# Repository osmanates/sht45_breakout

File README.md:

# SHT45 Breakout Kartı

Sensirion **SHT45** (±1.0 %RH, ±0.1 °C, I²C) nem ve sıcaklık sensörü için küçük bir breakout (modül) kartı.
Şema, PCB, Gerber, delik dosyası ve JLCPCB montaj (BOM/CPL) dosyaları bu depoda.

| Özellik | Değer |
|---|---|
| Kart boyutu | **16.0 × 19.8 mm**, 2 katman, 1.6 mm FR4, 2 adet M2 montaj deliği |
| Besleme | **1.08 … 3.6 V** (5 V ile çalışmaz, aşağıya bakın) |
| Arayüz | I²C, adres **0x44** (SHT45-AD1B), en fazla 1 MHz (Fm+) |
| Konnektör | J1: 1×4, 2.54 mm pin header, J2: 4 pinli JST XH (2.50 mm). İkisinde de sıra `VCC GND SCL SDA` |
| Parçalar | U1 SHT45 (DFN-4 1.5×1.5), C1 100 nF 0603, R1/R2 10 kΩ 0603, JP1 lehim köprüsü |

(Görseller KiCad'in değil, doğrudan üretilen Gerber dosyalarının `gerbv` ile çizilmiş halidir.
Alt yüz, kartın üstünden bakılıyormuş gibi gösterildiği için yazılar ters görünüyor. Düz okunan
hali `docs/pcb_bottom.png` dosyasında.)

## Tasarım kararları (Sensirion dokümanlarından)

Tasarımda şu belgeler kullanıldı: *Datasheet SHT4x v7.3*, *Design Guide for Humidity and
Temperature Sensors*, *Handling Instructions SHTxx*, *Contamination Guide*, *Creep Mitigation
SHT4x* ve *Heater Decontamination SHT4x* ([ürün sayfası](https://sensirion.com/products/catalog/SHT45)).

1. **Devre, datasheet Fig. 1'deki tipik uygulama devresiyle aynı:** SDA/SCL için 10 kΩ pull-up,
   VDD–VSS arasında 100 nF. Pull-up değeri, datasheet'teki minimum değerin (VDD ≥ 1.62 V için
   390 Ω) çok üzerinde.
2. **Land pattern datasheet Fig. 17'ye göre çizildi:** 0.5 × 0.3 mm pad'ler, 0.8 mm dikey ve 1.4 mm
   yatay aralık (KiCad'deki `Sensirion_DFN-4_…_SHT4x_NoCentralPad` footprint'i).
   **Orta pad (die pad) lehimlenmiyor** ve sensörün altında pad'ler dışında **bakır yok**
   (datasheet 5.3). Lehimlenmiş bir die pad, sensörün içindeki ısıtıcıyı soğutur (heat sink etkisi).
3. **Termal izolasyon:** Sensör, kartın geri kalanından iki adet 1.2 mm'lik freze yarığıyla ayrılmış
   4.4 mm genişliğinde bir "dil" üzerinde duruyor (Design Guide bölüm 3 / Fig. 8b, 11). Dile sadece 4 adet **0.15 mm**
   iz geçiyor. Dilde bakır dolgu (pour) yok. Böylece header'dan ve bağlı karttan gelen ısı sensöre
   daha az ulaşıyor.
4. **C1, sensörün VDD/VSS pinlerine doğrudan bağlı** (≈0.6 mm uzaklıkta). Isıtıcı çalışırken
   çekilen 100 mA'e varan akım darbeleri için bu yakınlık önemli.
5. **Pull-up'lar ve lehim köprüsü ana gövdede**, sensörden uzakta. **JP1** (alt yüzde, "PU")
   fabrikadan kapalı (köprülü) gelir. Aynı I²C hattında zaten pull-up varsa (ör. birden fazla
   modül kullanıyorsanız) iki pad arasındaki ince izi maket bıçağıyla kesin. Böylece iki pull-up
   birlikte devreden çıkar.
6. **Kolay kullanım için yaygın pin sırası** (`VCC GND SCL SDA`). Pin etiketleri iki yüzde de
   yazılı, 1 numaralı pin kare pad'li. Pin header (J1) ile JST XH (J2) aynı sütunlarda, J2
   hemen J1'in altında. İkisinden birini ya da ikisini birden takabilirsiniz.
7. **Montaj delikleri:** Dilin iki yanındaki "kulaklarda" 2 adet M2 delik (2.2 mm, kaplamasız)
   var. Kulaklar da dile değmiyor, böylece vidalanan yüzeyin sıcaklığı sensöre doğrudan geçmiyor.

## Dosyalar

```
hardware/                 KiCad 7 projesi (.kicad_pro / .kicad_sch / .kicad_pcb) + DRC raporu
production/
  sht45_breakout_gerbers.zip   → PCB siparişi için bunu yükleyin
  gerbers/                     açık hali (Gerber X2, Excellon, job dosyası)
  sht45_breakout_bom.csv       JLCPCB montaj BOM'u (LCSC numaralarıyla)
  sht45_breakout_cpl.csv       JLCPCB montaj pozisyon (CPL) dosyası
docs/                     şema PDF'i, PCB PDF/PNG görselleri
tools/                    tasarımı ve tüm çıktıları sıfırdan üreten betikler
```

Proje dosyaları KiCad 7 ile üretildi, KiCad 8 ve 9 ile de açılabilir. Şema ve PCB aynı UUID'lerle
bağlı, bu yüzden KiCad'de "Update PCB from Schematic" sorunsuz çalışır.

## JLCPCB siparişi

### Sadece PCB
1. <https://jlcpcb.com> → *Order now* → `production/sht45_breakout_gerbers.zip` dosyasını yükleyin.
2. Önerilen ayarlar: 2 Layers, FR-4, **1.6 mm** (termal kütleyi azaltmak isterseniz 1.0 mm de olur),
   renk serbest, yüzey kaplaması **ENIG** (0.5 × 0.3 mm'lik DFN pad'lerinde daha düz bir yüzey
   sağlar; HASL lead-free de çalışır).
3. *Remove Order Number* seçeneğini işaretleyin. Kartta sipariş numarasına uygun boş yer yok.
4. Kartta 2 adet 0.3 mm via, 8 adet konnektör deliği (1.0 ve 0.95 mm), 2 adet 2.2 mm kaplamasız
   montaj deliği ve 2 adet 1.2 mm frezelenmiş yarık var. Minimum iz/boşluk 0.15 mm.
   Bunların hepsi standart (ek ücretsiz) üretim sınırları içinde.

### Montajlı (PCBA), önerilen yöntem
SHT45 bacaksız, 1.5 mm'lik bir DFN kılıf. Sensirion **elle (havya ile) lehimlemeyi önermiyor**
(Handling Instructions). Bu yüzden en sorunsuz yol, kartları JLCPCB'ye dizdirmek:

1. PCB siparişinde *PCB Assembly* seçeneğini açın, *Top side* seçin.
2. BOM olarak `production/sht45_breakout_bom.csv`, CPL olarak `production/sht45_breakout_cpl.csv`
   dosyalarını yükleyin.

   | Ref | Parça | LCSC |
   |---|---|---|
   | U1 | SHT45-AD1B-R2 | C9900092421 |
   | C1 | 100 nF 0603 X7R | C14663 (basic) |
   | R1, R2 | 10 kΩ 0603 1% | C25804 (basic) |

3. **Önizleme ekranında U1'in yönünü kontrol edin:** pin-1 noktası, kart üstünde sensörün
   **sağ üst köşesindeki** üçgen işaretle aynı yerde olmalı. JLC'nin kütüphanesindeki DFN
   modelleri bazen 90°/180° kaymış gelebiliyor. Gerekirse önizlemede döndürün.
4. SHT45 stokta yoksa aynı footprint'e sahip **SHT45-AD1F-R2** (C5360602, üstü polyimid filtre
   zarlı, IP68) kullanılabilir. Parça numaralarını ve stok durumunu sipariş anında kontrol edin.
5. Konnektörler (J1, J2) ve JP1 montaj listesinde yok. Konnektörleri kendiniz lehimleyin, JP1 zaten bakır bir köprü.

> Not: Kart 10 × 10 mm'den büyük olduğu için tek parça olarak montaja uygun. JLC panelleme
> isterse sipariş ekranındaki *Panel by JLCPCB* seçeneği yeterli.

### Kendiniz dizecekseniz
Stencil ile no-clean pasta (Type 3 veya daha ince) sürüp hot-plate ya da sıcak hava kullanın
(tepe sıcaklık ≤ 260 °C). **Kartı yıkamayın, IPA ya da flux temizleyici kullanmayın**
(Handling Instructions: "Do not apply board wash"). Reflow'dan sonra ölçümde −1…−2 %RH'lik
bir sapma görülebilir, 1–3 gün içinde kendiliğinden kaybolur.

### Kendin dizmek için malzeme listesi (1 kart)

| Adet | Parça | Not |
|---|---|---|
| 1 | SHT45-AD1F-R2 veya SHT45-AD1B-R2 | F = üstü filtre zarlı, B = açık kılıf. Aynı footprint |
| 2 | 10 kΩ direnç, 0603 | R1, R2 (I²C pull-up) |
| 1 | 100 nF kondansatör, 0603, X7R, ≥10 V | C1 |
| 1 | 1×4 erkek pin header, 2.54 mm | J1, isteğe bağlı |
| 1 | JST XH 4 pin dik soket (B4B-XH-A) | J2, isteğe bağlı. "XH2.54" diye satılan klonlar da oturur |
| 2 | M2 vida + somun/spacer | İsteğe bağlı |

JP1 bir parça değil, bakır bir köprü. Lehim pastası no-clean olmalı.
Pasif parçalar 0603 seçildi, elle yerleştirmesi kolay.

## Kullanım

- **Sadece 3.3 V (veya daha düşük) sistemlerde doğrudan kullanın** (ESP32, RP2040, STM32,
  3.3 V Arduino'lar vb.). Pinlerdeki mutlak maksimum gerilim VDD + 0.3 V. 5 V'luk bir
  Arduino'da (Uno/Nano) VCC'yi 3.3 V pininden besleseniz bile Wire kütüphanesi SDA/SCL'yi
  dahili olarak 5 V'a çeker. Bu durumda bir **I²C seviye dönüştürücü** (ör. BSS138 modülü) kullanın.
- Adres **0x44**. Hazır kütüphaneler: Sensirion `arduino-i2c-sht4x`, Adafruit `Adafruit_SHT4x`,
  MicroPython/CircuitPython `adafruit_sht4x`.
- Datasheet'teki en basit okuma akışı:

  ```
  i2c_write(0x44, [0xFD])            # yüksek hassasiyetle ölç
  bekle(10 ms)
  d = i2c_read(0x44, 6)
  T  = -45 + 175 * (d[0]*256 + d[1]) / 65535      # °C
  RH =  -6 + 125 * (d[3]*256 + d[4]) / 65535      # %RH, 0..100 aralığına sınırlayın
  ```
- Dili kırmayın veya bükmeyin. Sensörün üstündeki açıklığı kapatmayın. Kartın konformal
  kaplamayla kaplanması gerekiyorsa sensörün üstünü koruyun (Kapton bant gibi).

## Yeniden üretme

Tasarım tamamen betiklerden oluşturuluyor. Ubuntu 24.04'te:

```bash
sudo apt install kicad poppler-utils zip gerbv   # KiCad 7.0
./tools/build.sh
```

- `tools/gen_schematic.py`: şemayı yazar.
- `tools/gen_pcb.py`: kart şeklini, yerleşimi ve yolları pcbnew API ile oluşturur. Pad
  konumlarını kontrol eder.
- `tools/drc.py`: DRC çalıştırır (`hardware/drc_report.txt`).
- `tools/jlc_assembly.py`: JLCPCB BOM/CPL dosyalarını oluşturur.
- `tools/render.py`: PNG önizlemelerini üretir.

## Doğrulama durumu

- KiCad DRC: **0 hata, 0 bağlantısız pad.** Kalan tek uyarı, J1 footprint'inin kütüphanedeki
  halinden farklı olması. Bunun sebebi, pin etiketlerine yer açmak için header'ın silkscreen
  çerçevesini bilinçli olarak kaldırmam.
- Şema ile PCB netlist'i betikle karşılaştırıldı, birebir aynı.
- Gerber ve delik dosyaları bağımsız bir görüntüleyicide (gerbv) açılıp kontrol edildi.
- Kart henüz fiziksel olarak üretilip test edilmedi. İlk siparişte az adet ile başlamanız önerilir.

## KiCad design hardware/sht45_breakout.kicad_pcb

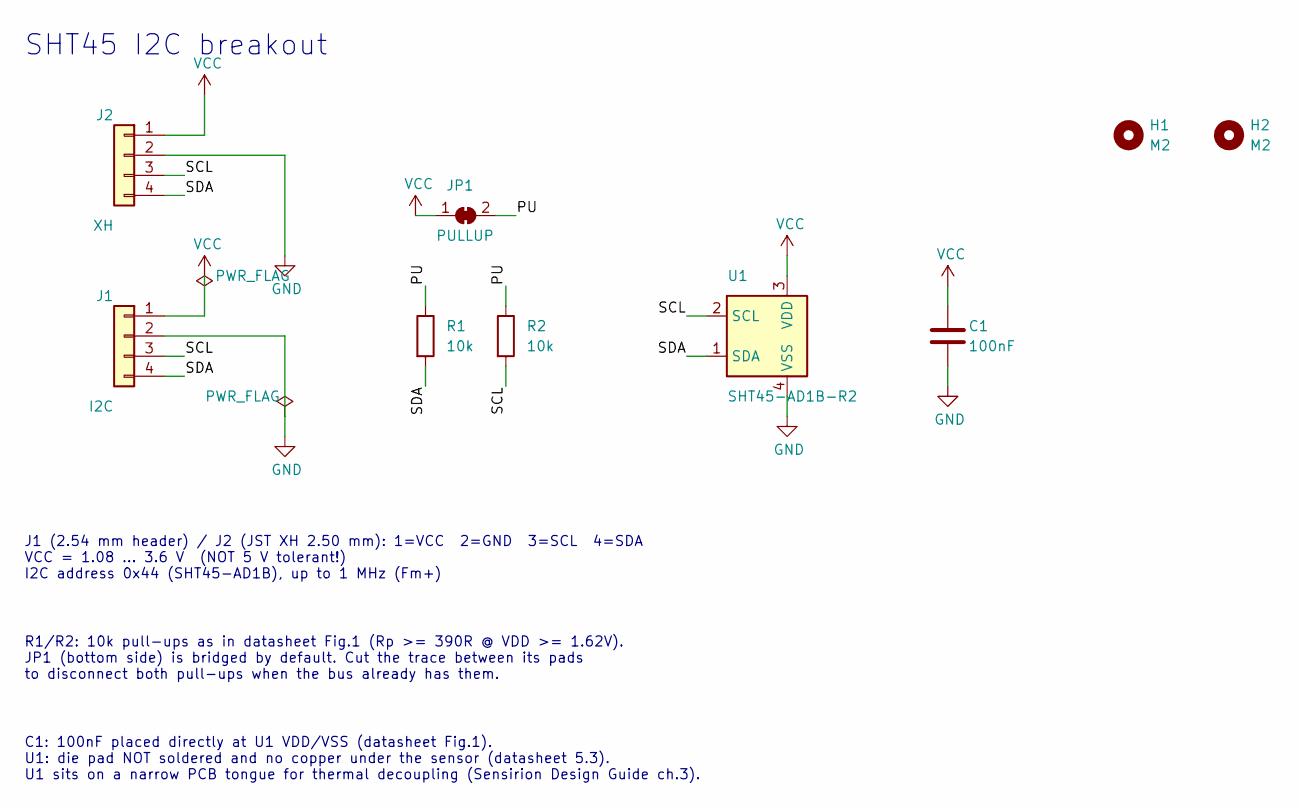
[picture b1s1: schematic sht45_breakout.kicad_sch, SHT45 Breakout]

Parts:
C1: 100nF; C_0603_1608Metric; Voltage 50V; LCSC C14663
H1, H2: M2; MountingHole_2.2mm_M2
J1: I2C; PinHeader_1x04_P2.54mm_Vertical
J2: XH; JST_XH_B4B-XH-A_1x04_P2.50mm_Vertical
JP1: PULLUP; SolderJumper-2_P1.3mm_Bridged_RoundedPad1.0x1.5mm
R1, R2: 10k; R_0603_1608Metric; Tolerance 1%; LCSC C25804
U1: SHT45-AD1B-R2; Sensirion_DFN-4_1.5x1.5mm_P0.8mm_SHT4x_NoCentralPad; MPN SHT45-AD1B-R2; LCSC C9900092421

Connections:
/PU: JP1.2 (B), R1.1, R2.1
/SCL: J1.3, J2.3, R2.2, U1.2 (SCL)
/SDA: J1.4, J2.4, R1.2, U1.1 (SDA)
GND: C1.2, J1.2, J2.2, U1.4 (VSS)
VCC: C1.1, J1.1, J2.1, JP1.1 (A), U1.3 (VDD)

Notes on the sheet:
SHT45 I2C breakout
J1 (2.54 mm header) / J2 (JST XH 2.50 mm): 1=VCC 2=GND 3=SCL 4=SDA VCC = 1.08 ... 3.6 V (NOT 5 V tolerant!) I2C address 0x44 (SHT45-AD1B), up to 1 MHz (Fm+)
R1/R2: 10k pull-ups as in datasheet Fig.1 (Rp >= 390R @ VDD >= 1.62V). JP1 (bottom side) is bridged by default. Cut the trace between its pads to disconnect both pull-ups when the bus already has them.
C1: 100nF placed directly at U1 VDD/VSS (datasheet Fig.1). U1: die pad NOT soldered and no copper under the sensor (datasheet 5.3). U1 sits on a narrow PCB tongue for thermal decoupling (Sensirion Design Guide ch.3).

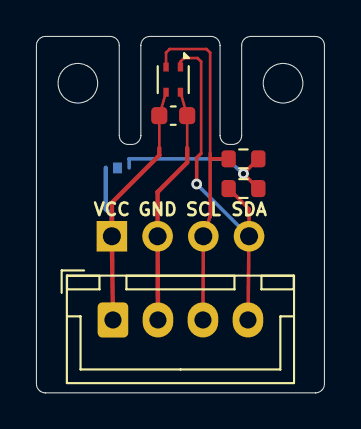
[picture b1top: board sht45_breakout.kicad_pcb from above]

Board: 2 copper layers, 16.0 x 19.8 mm, 9 parts (1 on the bottom side), 5 nets.

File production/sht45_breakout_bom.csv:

Comment,Designator,Footprint,LCSC Part #
100nF,C1,C_0603_1608Metric,C14663
10k,"R1,R2",R_0603_1608Metric,C25804
SHT45-AD1B-R2,U1,Sensirion_DFN-4_1.5x1.5mm_P0.8mm_SHT4x_NoCentralPad,C9900092421
